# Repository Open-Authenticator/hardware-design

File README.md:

# Open Authenticator Hardware Design

This repository contains hardware design files and datasheets for the open authenticator. This project is in development and is not ready for release.

<a href="https://oshpark.com/shared_projects/XT2lydtr"></img></a>

## Features

* Small form factor of 82mm x 42mm
* Uses ESP32-WROOM-32D module
* Uses 128x64 0.96" inch OLED panel
* Uses DS3231 RTC with battery backup (CR2032) for timekeeping
* Powered by 3.7V 300 mAh LiPo battery
* Uses MCP73831 for charging LiPo battery
* Uses TPS63001 Buck Boost Converter IC for efficient 3.3V power supply, with input range from 1.8V - 5.5V
* Uses TPS22919 Load switch to control power to OLED and RTC chip
* Autoselect power source, i.e., battery or USB
* USB Type-C for charging only (no data pins connected)

## Project Structure

```
/datasheets - contains datasheets of various components used in the pcb
/kicad_project - contains kicad project files for the pcb
/schematics - contains schematics of the the pcb
```

## Tools

To view/modify the files from this repository, install KiCAD from: [https://kicad.org](https://kicad.org)

## Schematics

## Plots

### Front side

### Back side

## Credits

Thanks to OSHPark for sponsoring first prototypes

Thanks to PCBway for sponsoring the final prototypes

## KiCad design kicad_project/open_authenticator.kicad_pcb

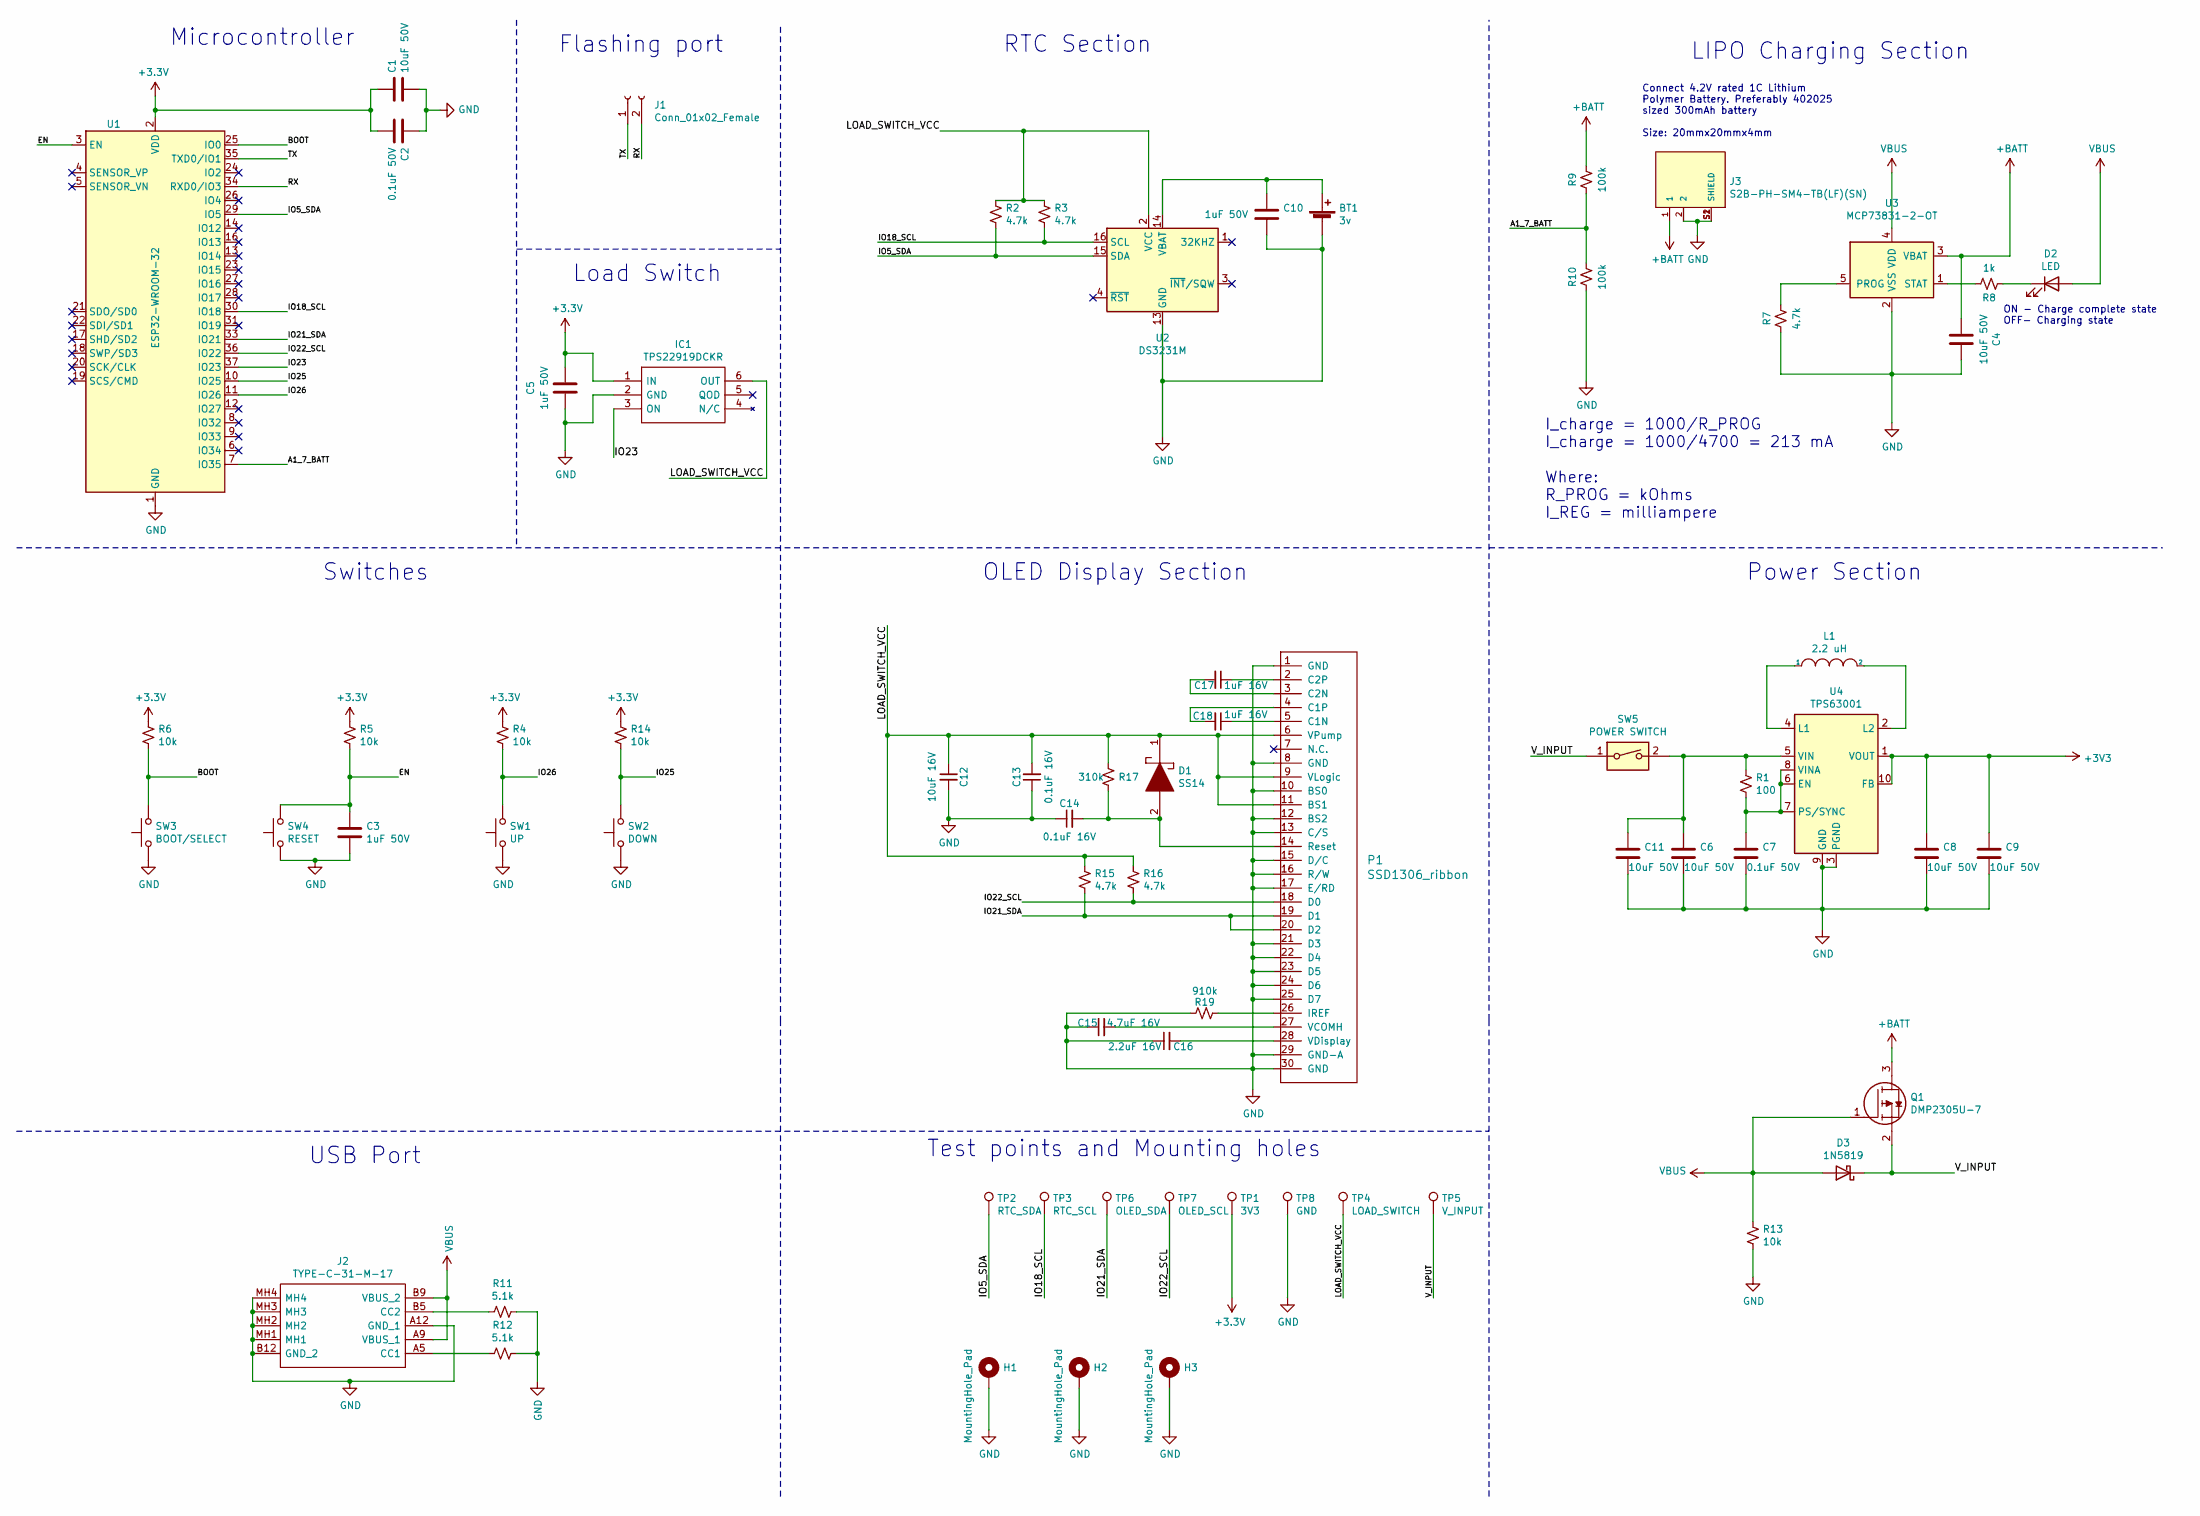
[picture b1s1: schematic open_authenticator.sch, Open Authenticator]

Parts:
BT1: 3v; CR2032BS61
C1, C4, C6, C8, C9, C11: 10uF 50V; C_1206_3216Metric
C2, C7: 0.1uF 50V; C_1206_3216Metric
C3, C5, C10: 1uF 50V; C_1206_3216Metric
C12: 10uF 16V; C_0603_1608Metric
C13, C14: 0.1uF 16V; C_0603_1608Metric
C15: 4.7uF 16V; C_0603_1608Metric
C16: 2.2uF 16V; C_0603_1608Metric
C17, C18: 1uF 16V; C_0603_1608Metric
D1: SS14; DIOM5227X270N; Manufacturer_Part_Number SS14; Mouser Part Number 512-SS14
D2: LED; LED_0603_1608Metric_Castellated
D3: 1N5819; D_SOD-123
H1, H2, H3: MountingHole_Pad; MountingHole_2.2mm_M2_ISO7380_Pad
IC1: TPS22919DCKR; SOT65P210X110-6N; Manufacturer_Part_Number TPS22919DCKR; Mouser Part Number 595-TPS22919DCKR
J1: Conn_01x02_Female; PinHeader_1x02_P2.54mm_Vertical
J2: TYPE-C-31-M-17; TYPEC31M17; Manufacturer_Part_Number TYPE-C-31-M-17
J3: S2B-PH-SM4-TB(LF)(SN); JST_S2B-PH-SM4-TB(LF)(SN)
L1: 2.2 uH; INDPM102100X400N
P1: SSD1306_ribbon
Q1: DMP2305U-7; SOT96P240X110-3N; Manufacturer_Part_Number DMP2305U-7; Mouser Part Number 621-DMP2305U-7
R1: 100; R_0603_1608Metric
R2, R3, R7, R15, R16: 4.7k; R_0603_1608Metric
R4, R5, R6, R13, R14: 10k; R_0603_1608Metric
R8: 1k; R_0603_1608Metric
R9, R10: 100k; R_0603_1608Metric
R11, R12: 5.1k; R_0603_1608Metric
R17: 310k; R_0603_1608Metric
R19: 910k; R_0603_1608Metric
SW1: UP; SW_Push_1P1T_NO_6x6mm_H9.5mm
SW2: DOWN; SW_Push_1P1T_NO_6x6mm_H9.5mm
SW3: BOOT/SELECT; SW_Push_1P1T_NO_6x6mm_H9.5mm
SW4: RESET; SW_Push_1P1T_NO_6x6mm_H9.5mm
SW5: POWER SWITCH; Slide_Switch_SS-12D00
TP1: 3V3; SolderWirePad_1x01_SMD_1x2mm
TP2: RTC_SDA; SolderWirePad_1x01_SMD_1x2mm
TP3: RTC_SCL; SolderWirePad_1x01_SMD_1x2mm
TP4: LOAD_SWITCH; SolderWirePad_1x01_SMD_1x2mm
TP5: V_INPUT; SolderWirePad_1x01_SMD_1x2mm
TP6: OLED_SDA; SolderWirePad_1x01_SMD_1x2mm
TP7: OLED_SCL; SolderWirePad_1x01_SMD_1x2mm
TP8: GND; SolderWirePad_1x01_SMD_1x2mm
U1: ESP32-WROOM-32
U2: DS3231M; SOIC-16W_7.5x10.3mm_P1.27mm
U3: MCP73831-2-OT; SOT-23-5
U4: TPS63001; Texas_DRC0010J_ThermalVias

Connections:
+BATT: C4.2, J3.1, Q1.3, R9.1, U3.3 (VBAT)
/A1_7_BATT: R9.2, R10.1, U1.7 (IO35)
/BOOT: R6.2, SW3.2, U1.25 (IO0)
/EN: C3.1, R5.2, SW4.2, U1.3 (EN)
/IO5_SDA: R2.2, TP2.1, U1.29 (IO5), U2.15 (SDA)
/IO18_SCL: R3.2, TP3.1, U1.30 (IO18), U2.16 (SCL)
/IO21_SDA: P1.19 (D1), P1.20 (D2), R15.2, TP6.1, U1.33 (IO21)
/IO22_SCL: P1.18 (D0), R16.2, TP7.1, U1.36 (IO22)
/IO23: IC1.3 (ON), U1.37 (IO23)
/IO25: R14.2, SW2.2, U1.10 (IO25)
/IO26: R4.2, SW1.2, U1.11 (IO26)
/LOAD_SWITCH_VCC: C12.1, C13.2, D1.1, IC1.6 (OUT), P1.6 (VPump), P1.9 (VLogic), P1.11 (BS1), R2.1, R3.1, R15.1, R16.1, R17.1, TP4.1, U2.2 (VCC)
/RX: J1.2, U1.34 (RXD0/IO3)
/TX: J1.1, U1.35 (TXD0/IO1)
/V_INPUT: D3.1 (K), Q1.2, SW5.1, TP5.1
GND: BT1.2 (-), C1.2, C2.1, C3.2, C4.1, C5.1, C6.2, C7.2, C8.2, C9.2, C10.2, C11.2, C12.2, C13.1, C14.1, C15.1, C16.1, H1.1, H2.1, H3.1, IC1.2 (GND), J2.A12 (GND_1), J2.B12 (GND_2), J2.MH1, J2.MH2, J2.MH3, J2.MH4, J3.2, J3.S1 (SHIELD), J3.S2 (SHIELD), P1.1 (GND), P1.8 (GND), P1.10 (BS0), P1.12 (BS2), P1.13 (C/S), P1.15 (D/C), P1.16 (R/W), P1.17 (E/RD), P1.21 (D3), P1.22 (D4), P1.23 (D5), P1.24 (D6), P1.25 (D7), P1.29 (GND-A), P1.30 (GND), R7.2, R10.2, R11.1, R12.1, R13.2, R19.1, SW1.1, SW2.1, SW3.1, SW4.1, TP8.1, U1.1 (GND), U1.15 (GND), U1.38 (GND), U1.39 (GND), U2.5 (GND), U2.6 (GND), U2.7 (GND), U2.8 (GND), U2.9 (GND), U2.10 (GND), U2.11 (GND), U2.12 (GND), U2.13 (GND), U3.2 (VSS), U4.3 (PGND), U4.9 (GND), U4.11 (PGND)
unnamed: BT1.1 (+), C10.1, U2.14 (VBAT)
unnamed: C7.1, R1.2, U4.6 (EN), U4.7 (PS/SYNC), U4.8 (VINA)
unnamed: C6.1, C11.1, R1.1, SW5.2, U4.5 (VIN)
unnamed: C14.2, D1.2, P1.14 (Reset), R17.2
unnamed: C15.2, P1.27 (VCOMH)
unnamed: C16.2, P1.28 (VDisplay)
unnamed: C17.1, P1.2 (C2P)
unnamed: C17.2, P1.3 (C2N)
unnamed: C18.1, P1.5 (C1N)
unnamed: C18.2, P1.4 (C1P)
unnamed: D2.1 (K), R8.2
unnamed: J2.A5 (CC1), R12.2
unnamed: J2.B5 (CC2), R11.2
unnamed: L1.1, U4.4 (L1)
unnamed: L1.2, U4.2 (L2)
unnamed: P1.26 (IREF), R19.2
unnamed: R7.1, U3.5 (PROG)
unnamed: R8.1, U3.1 (STAT)
VBUS: D2.2 (A), D3.2 (A), J2.A9 (VBUS_1), J2.B9 (VBUS_2), Q1.1, R13.1, U3.4 (VDD)

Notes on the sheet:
Microcontroller
Flashing port
RTC Section
OLED Display Section
Switches
Load Switch
LIPO Charging Section
Power Section
USB Port
Test points and Mounting holes
ON - Charge complete state OFF- Charging state
I_charge = 1000/R_PROG I_charge = 1000/4700 = 213 mA Where: R_PROG = kOhms I_REG = milliampere
Connect 4.2V rated 1C Lithium Polymer Battery. Preferably 402025 sized 300mAh battery Size: 20mmx20mmx4mm

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
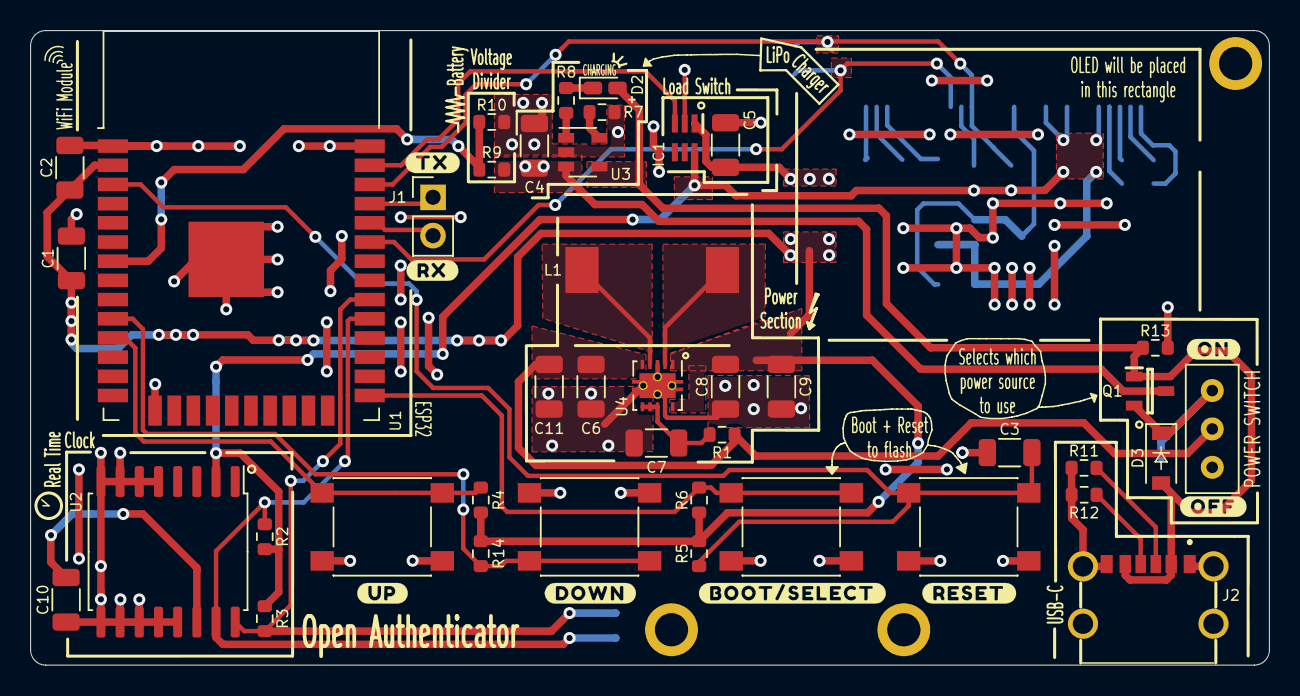
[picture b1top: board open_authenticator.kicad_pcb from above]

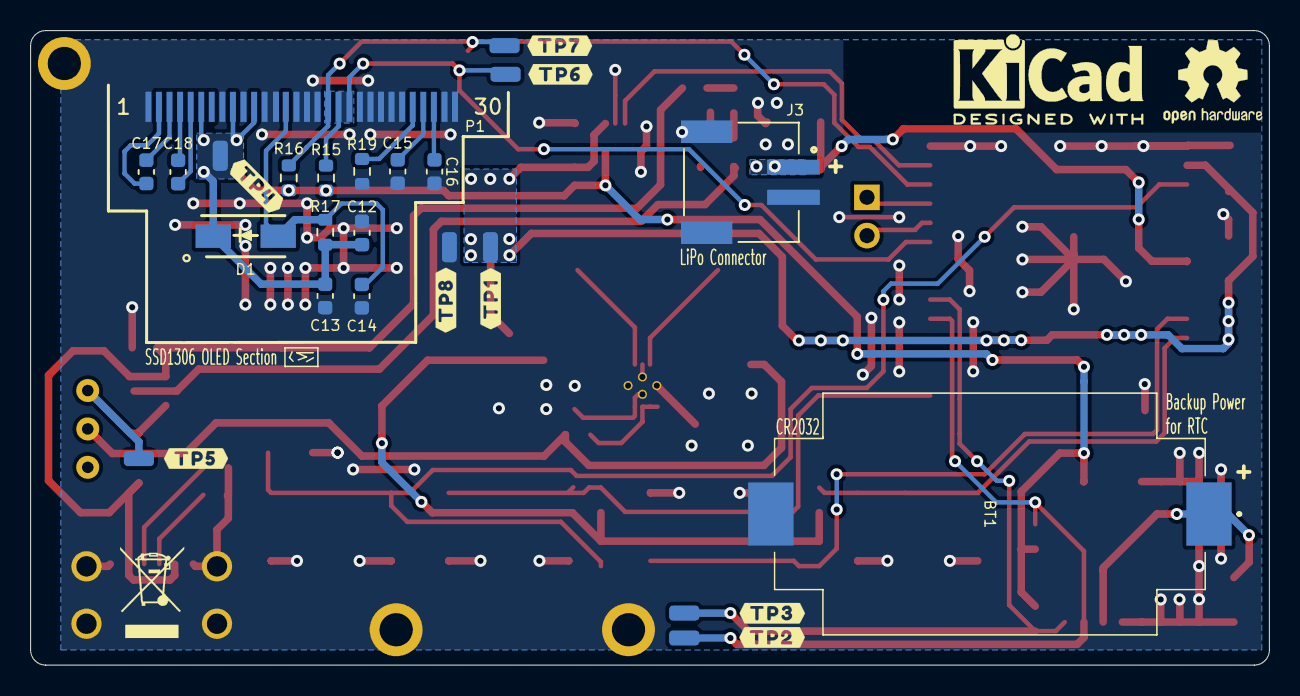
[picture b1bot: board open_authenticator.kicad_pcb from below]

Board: 2 copper layers, 82.0 x 42.0 mm, 67 parts (23 on the bottom side), 36 nets.

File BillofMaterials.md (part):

|                      |                                                            |                 |                                |                                                          |                                                                                                             |      |
|----------------------|------------------------------------------------------------|-----------------|--------------------------------|----------------------------------------------------------|-------------------------------------------------------------------------------------------------------------|------|
|Ref                   |Qnty                                                        |Value            |Cmp name                        |Footprint                                                 |Description                                                                                                  |Vendor|
|Brd1,                 |1                                                           |SSD1306          |SSD1306                         |SSD1306:128x64OLED                                        |SSD1306 OLED                                                                                                 |      |
|BT1,                  |1                                                           |3v               |Battery_Cell-Device             |BU2032SM-BT-GTR:BU2032SMBTGTR                             |                                                                                                             |      |
|C3, C5,               |2                                                           |1uF              |C-Device                        |Capacitor_SMD:C_1206_3216Metric                           |                                                                                                             |      |
|C4, C6, C8, C9,       |4                                                           |10uF             |C-Device                        |Capacitor_SMD:C_1206_3216Metric                           |                                                                                                             |      |
|C7,                   |1                                                           |0.1uF            |C-Device                        |Capacitor_SMD:C_1206_3216Metric                           |                                                                                                             |      |
|D2,                   |1                                                           |LED              |LED-Device                      |LED_SMD:LED_0603_1608Metric_Castellated                   |                                                                                                             |      |
|D3,                   |1                                                           |1N5819           |1N5819-Diode                    |Diode_SMD:D_SOD-123                                       |                                                                                                             |      |
|IC1,                  |1                                                           |TPS22919DCKR     |TPS22919DCKR                    |TPS22919DCKR:SOT65P210X110-6N                             |5.5V, 1.5A, 90m self-protected load switch with controlled rise time                                         |      |
|J1,                   |1                                                           |Conn_01x06_Female|Conn_01x06_Female-Connector     |Connector_PinHeader_2.00mm:PinHeader_1x06_P2.00mm_Vertical|                                                                                                             |      |
|J2,                   |1                                                           |TYPE-C-31-M-17   |TYPE-C-31-M-17                  |TYPE-C-31-M-17:TYPEC31M17                                 |USB Connectors 6 Receptacle 1 RoHS                                                                           |      |
|L1,                   |1                                                           |2.2 uH           |INDUCTOR-pspice                 |CDRH104RNP-150NC:INDPM102100X400N                         |                                                                                                             |      |
|Q1,                   |1                                                           |DMP2305U-7       |DMP2305U-7                      |DMP2305U-7:SOT96P240X110-3N                               |MOSFET P-Channel 20V 4.2A SOT23 Diodes Inc DMP2305U-7 P-channel MOSFET Transistor, 4.2 A, -20 V, 3-Pin SOT-23|      |
|R1,                   |1                                                           |100              |R_Small_US-Device               |Resistor_SMD:R_0603_1608Metric                            |                                                                                                             |      |
|R2, R3, R7,           |3                                                           |4.7k             |R_Small_US-Device               |Resistor_SMD:R_0603_1608Metric                            |                                                                                                             |      |
|R4, R5, R6, R13, R14, |5                                                           |10k              |R_Small_US-Device               |Resistor_SMD:R_0603_1608Metric                            |                                                                                                             |      |
|R8,                   |1                                                           |1k               |R_Small_US-Device               |Resistor_SMD:R_0603_1608Metric                            |                                                                                                             |      |
|R9, R10,              |2                                                           |100k             |R_Small_US-Device               |Resistor_SMD:R_0603_1608Metric                            |                                                                                                             |      |
|R11, R12,             |2                                                           |5.1k             |R_Small_US-Device               |Resistor_SMD:R_0603_1608Metric                            |                                                                                                             |      |
|SW1, SW2,             |2                                                           |SW_Push          |SW_Push-Switch                  |Button_Switch_SMD:SW_Push_1P1T_NO_6x6mm_H9.5mm            |                                                                                                             |      |
|SW3,                  |1                                                           |BOOT             |SW_Push-Switch                  |Button_Switch_SMD:SW_Push_1P1T_NO_6x6mm_H9.5mm            |                                                                                                             |      |
|SW4,                  |1                                                           |RESET            |SW_Push-Switch                  |Button_Switch_SMD:SW_Push_1P1T_NO_6x6mm_H9.5mm            |                                                                                                             |      |
|U1,                   |1                                                           |ESP32-WROOM-32   |ESP32-WROOM-32-RF_Module        |RF_Module:ESP32-WROOM-32                                  |                                                                                                             |      |
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
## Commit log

2020-11-12 Added hardware dessign files
2020-11-15 Updated schematics - removed coin cell charging circuit
2020-11-15 Removed redundant rcapaciors
2020-11-16 Completed footprint association and generated Bill of materials
2020-11-16 Changed dmp2045u with cheaper dmp2305u and added pull resistor to switches
2020-11-16 Started layout of components. Fixed the Edge cut of PCB and rough location of components. Routing is yet to be done
2020-11-17 Renamed auto generated bill
2020-11-18 Partially completed routing
2020-11-19 Addede datasheets and partially completed routing
2020-11-19 Completed PCB routing
2020-11-21 Updated schematics according review feedback
2020-11-21 Updated schematics to add lipo output current
2020-11-22 Partially completed rerouting
2020-11-25 Partially completed routing, regulator section remains
2020-11-26 Updated pcb design to reduce routes in the ground plane
2020-11-26 Bridged the splits under the voltage regulator
2020-11-26 Minor fixes - Removed routes with 90 degree turns
2020-11-26 Completed pcb routing, minor touch ups and placing testpoints remaining
2020-11-26 Removed thermal relief from ground plane as not using any tht components
2020-11-27 Updated schematics by adding one more filter capacitor to voltage regulator VIN and changed routing accordingly
2020-11-27 Completed routing pcb
2020-11-28 Changed thermal via sizes to match manufacturer specs
2020-11-29 Removed test point from paste layer
2020-11-30 Updated pcb to increase rx/tx header size
2020-12-01 Replaced footprint of switch with custom made
2020-12-01 Added .gitignore file
2020-12-01 Removed files excluded from gitignore
2020-12-01 Restructered project
2020-12-01 Renamed component libraries and addded datasheets
2020-12-01 Updated .gitignore, added LICENSE and README
2020-12-01 Updated KiCad project with new path to component libraries
2020-12-01 Added plots and schematics to readme
2020-12-01 Minor fix to README
2020-12-01 renamed kicad project
2020-12-01 Updated README with Features section
2020-12-01 Added raytraced 3d rendering to readme
2020-12-01 Minor fix to README and added raytraced rendering of board
2020-12-02 Added gerber files
2020-12-05 Updated PCB and gerber, also added datasheet of battery
2020-12-16 Added interpolated points of discharge curve graph
2021-01-10 Added order from oshpark badge
2021-01-12 Updated placement of certain components and pads
2021-01-12 Added ssd1306 bare panel component
2021-01-14 Added datasheet of battery holder
2021-01-15 Added 3D-models of majority components and added schematics of bare oled-panel, assigned footprints, routing is to be done
2021-01-15 Create 3dModels
2021-01-15 Oled
2021-01-15 Moved oled step model to right place
2021-01-15 Added 3d model for oled, and rerouted to reduce jumpovers and optimize current path
2021-01-15 Optimized routing further, used copper fill zones to change plane for routes with power
2021-01-15 Fixed silkscreen issues
2021-01-15 Assigned OLED 3d model to it's footprint and moved USB-C port towards the edge
2021-01-15 Changed footprints of capacitors used in OLED sub circuit
2021-01-15 [WIP] Started routing components used for OLED sub circuit
2021-01-16 Routed components of OLED sub circuit, optimised routing further (major: removed 3v3 line going under the regulator
2021-01-16 Optimised routing near slide switch
2021-01-16 Minor fix to routing and added artistic silkscreen drawings
2021-01-18 Updated silkscreen with symbols, and a bit of art
2021-01-18 Completed work on F.Cu Layer and F.Silk
2021-01-18 Added mounting holes in schematics
2021-01-18 Placed mounting holes on the board
2021-01-18 Finished cleaning up bottom layer, silkscreen also updated
2021-01-19 Added lipo battery connector to schematics
2021-01-20 Added lipo connector to board and placed it accordingly
2021-01-20 Updated schematics to include info about battery
2021-01-20 Moved oled subcircuit so as to better fit the OLED on board
2021-01-22 Added ssd1306 datasheet
2021-01-22 Updated schematics of v1.4
2021-01-22 Updated silkscreen to include bounds of the OLED
2021-01-27 creates render files
2021-01-28 Fixed DRC warnings
2021-01-28 Minor changes to pcb and gerber files added
2021-01-28 Updated 3d model of usb-type-c
2021-01-28 Updated board design according to review
2021-02-02 updates blue renders
2021-02-02 export vrml with usb-c conn
2021-02-02 removes old usb conn
2021-02-02 create usb-c stl and add to blender
2021-02-02 adds usb-c conn to render
2021-02-19 Updated renders and schematics in .svg format
2021-02-19 Minor fix to README.md
2021-03-15 Changed R17 from 4.7k -> 310k in schematics to fix OLED Reset Issue
2021-03-15 Updated value of R17 in routing and regenerated schematics
2021-03-15 Updated gerber files
2021-08-23 Updated routing of R14 and R15

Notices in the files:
kicad_project/open_authenticator.kicad_pcb:
License: MIT
kicad_project/open_authenticator.sch:
License: MIT License
